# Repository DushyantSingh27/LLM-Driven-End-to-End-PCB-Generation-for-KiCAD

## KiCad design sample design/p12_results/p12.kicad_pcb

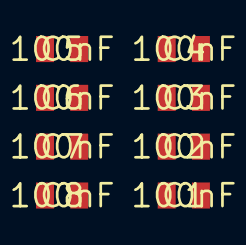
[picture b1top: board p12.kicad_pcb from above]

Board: 2 copper layers, 8 parts (0 on the bottom side), 2 nets, no tracks yet.

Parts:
C1, C2, C3, C4, C5, C6, C7, C8: 100nF; C_0805

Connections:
PGND: C1.2, C2.2, C3.2, C4.2, C5.2, C6.2, C7.2, C8.2
VBUS+: C1.1, C2.1, C3.1, C4.1, C5.1, C6.1, C7.1, C8.1

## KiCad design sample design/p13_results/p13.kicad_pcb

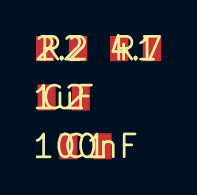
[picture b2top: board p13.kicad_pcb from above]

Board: 2 copper layers, 4 parts (0 on the bottom side), 3 nets, no tracks yet.

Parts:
C1: 100nF; C_0805
C2: 1uF; C_0805
R1: 4.7; R_0805
R2: 2.2; R_0805

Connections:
GATE: R1.2, R2.2
PGND: C1.2, C2.2
VCC: C1.1, C2.1

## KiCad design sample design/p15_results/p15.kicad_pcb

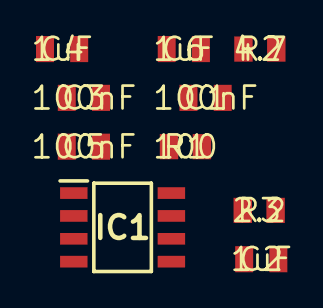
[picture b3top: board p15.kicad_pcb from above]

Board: 2 copper layers, 10 parts (0 on the bottom side), 8 nets, no tracks yet.

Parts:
C1, C3, C5: 100nF; C_0805
C2, C4, C6: 1uF; C_0805
IC1: UCC5390E
R1: 100; R_0805
R2: 4.7; R_0805
R3: 2.2; R_0805

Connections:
DRV_OUT: IC1.6, R2.1
GATE: R2.2, R3.2
GND1: C1.2, C2.2, IC1.3, IC1.4
GND2: C3.2, C4.2, C5.1, C6.1, IC1.7
unnamed: IC1.2, R1.2
VCC2: C3.1, C4.1, IC1.5
VCCI: C1.1, C2.1, IC1.1
VEE2: C5.2, C6.2, IC1.8

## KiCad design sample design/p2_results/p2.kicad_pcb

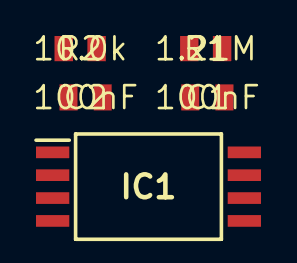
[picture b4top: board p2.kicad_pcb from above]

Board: 2 copper layers, 5 parts (0 on the bottom side), 5 nets, no tracks yet.

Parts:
C1, C2: 100nF; C_0805
IC1: AMC1350
R1: 1.21M; R_0805
R2: 10.0k; R_0805

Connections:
GND1: C1.2, IC1.3, IC1.4, R2.2
GND2: C2.2, IC1.5
VDD1: C1.1, IC1.1
VDD2: C2.1, IC1.8
VIN_DIV: IC1.2, R1.2, R2.1

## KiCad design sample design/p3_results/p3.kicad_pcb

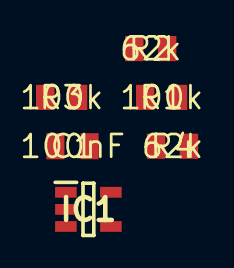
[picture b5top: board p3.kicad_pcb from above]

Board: 2 copper layers, 6 parts (0 on the bottom side), 5 nets, no tracks yet.

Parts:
C1: 100nF; C_0805
IC1: OPA328
R1, R3: 100k; R_0805
R2, R4: 62k; R_0805

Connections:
GND: C1.2, IC1.2
unnamed: IC1.4, R1.2, R2.2
unnamed: IC1.3, R3.2, R4.2
VDD: C1.1, IC1.5
VOUT: IC1.1, R2.1
